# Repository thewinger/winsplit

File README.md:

# Winsplit

Inspired by the Boardrun Bizarre and Red herring. I wanted to be able to use a normal keyset, so no full ortho, but split.

## Disclaimer

This is my first designed keyboard from the grounds up.
I'm not responsible for any damage caused by using this keyboard or any production of this keyboard that doesn't work.

## Bill of materials

To be bought separately:

- 2x [RP2040 Pro Micro](https://es.aliexpress.com/item/1005006130019224.html).
- 70x pin headers
- 1x [Skyloong Rotary Encoder](https://es.aliexpress.com/item/1005005189266585.html?spm=a2g0o.order_list.order_list_main.122.376d194dW3x576&gatewayAdapt=glo2esp).
- 2x [TRRS Connector](https://es.aliexpress.com/item/33029465106.html).
- 2x [SMD Buttons](https://es.aliexpress.com/item/33013562004.html).
- 2x 128x32 [OLED panels](https://es.aliexpress.com/item/1005005973981064.html?spm=a2g0o.order_list.order_list_main.167.376d194dW3x576&gatewayAdapt=glo2esp).
- 73x [Kailh hotswap sockets](https://es.aliexpress.com/item/1005004290562374.html?spm=a2g0o.order_list.order_list_main.178.376d194dW3x576&gatewayAdapt=glo2esp).
- 73x [SK6812MINI-E leds](https://es.aliexpress.com/item/1005004908622116.html?spm=a2g0o.order_list.order_list_main.147.376d194dW3x576&gatewayAdapt=glo2esp).
- 4x 2u Stabilizers.
- 16x M2 6mm screws.

Diodes, capacitors, resistors and other small parts are to be soldered directly by JLCPCB. References in KiCad files.

## TODO

- [ ] **Rotate 180º right-side OLED connector.** Right now is not usable.
- [ ] **Rotary encoder.** As of now, it either works as a button when a normal switch is installed or as an encoder without button when the HS Skyloong encoder is installed.
- [ ] **Make screw holes in PCB 4mm instead of 2.2mm.** So they are passthrougth and bottom plate can be directly screwed to top plate, like lily58 or Corne keyboards.

## Notes

- Function keys (Right of B and left of N) are hard to reach.

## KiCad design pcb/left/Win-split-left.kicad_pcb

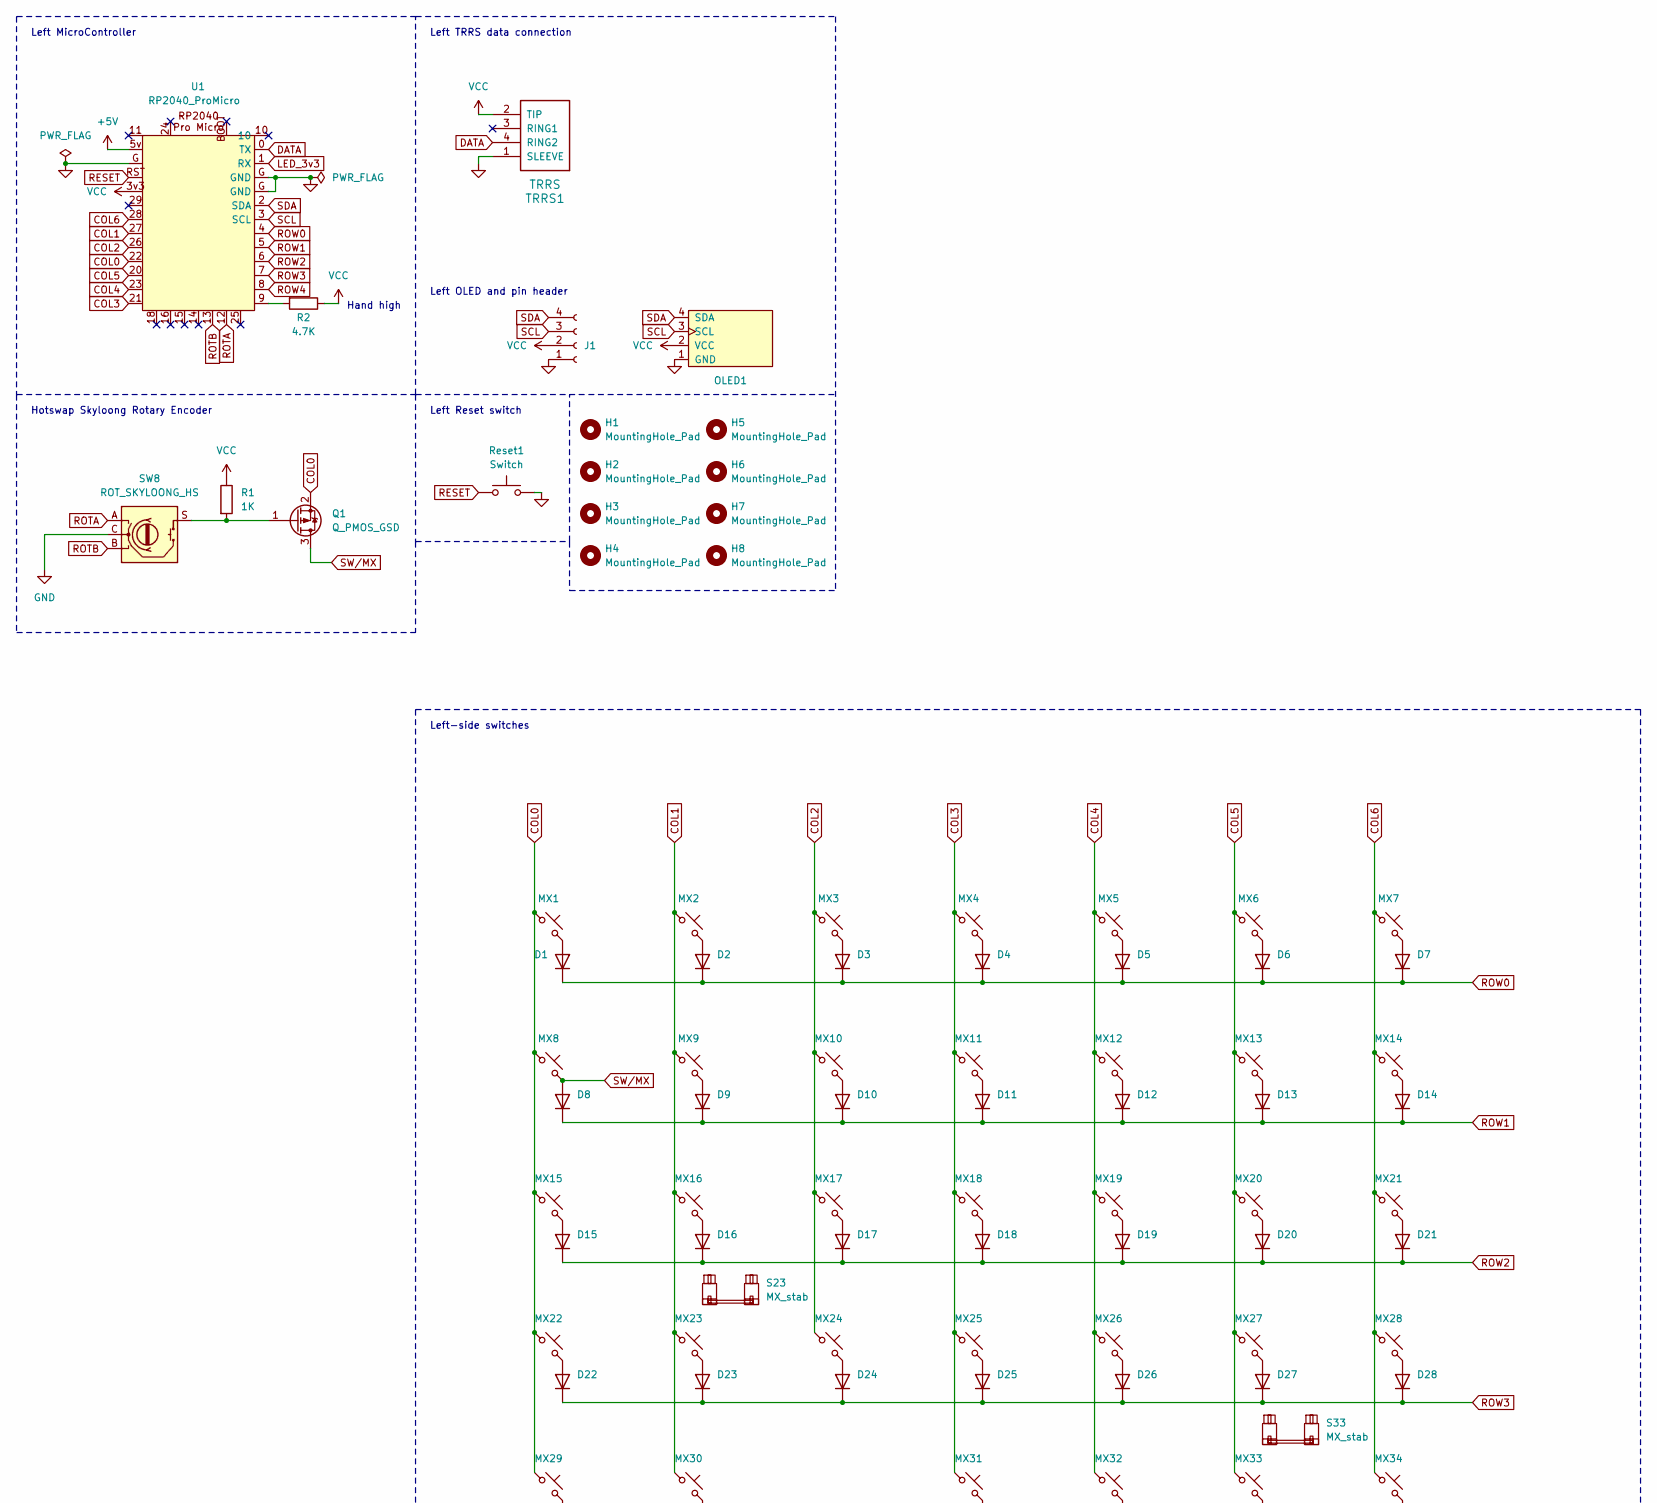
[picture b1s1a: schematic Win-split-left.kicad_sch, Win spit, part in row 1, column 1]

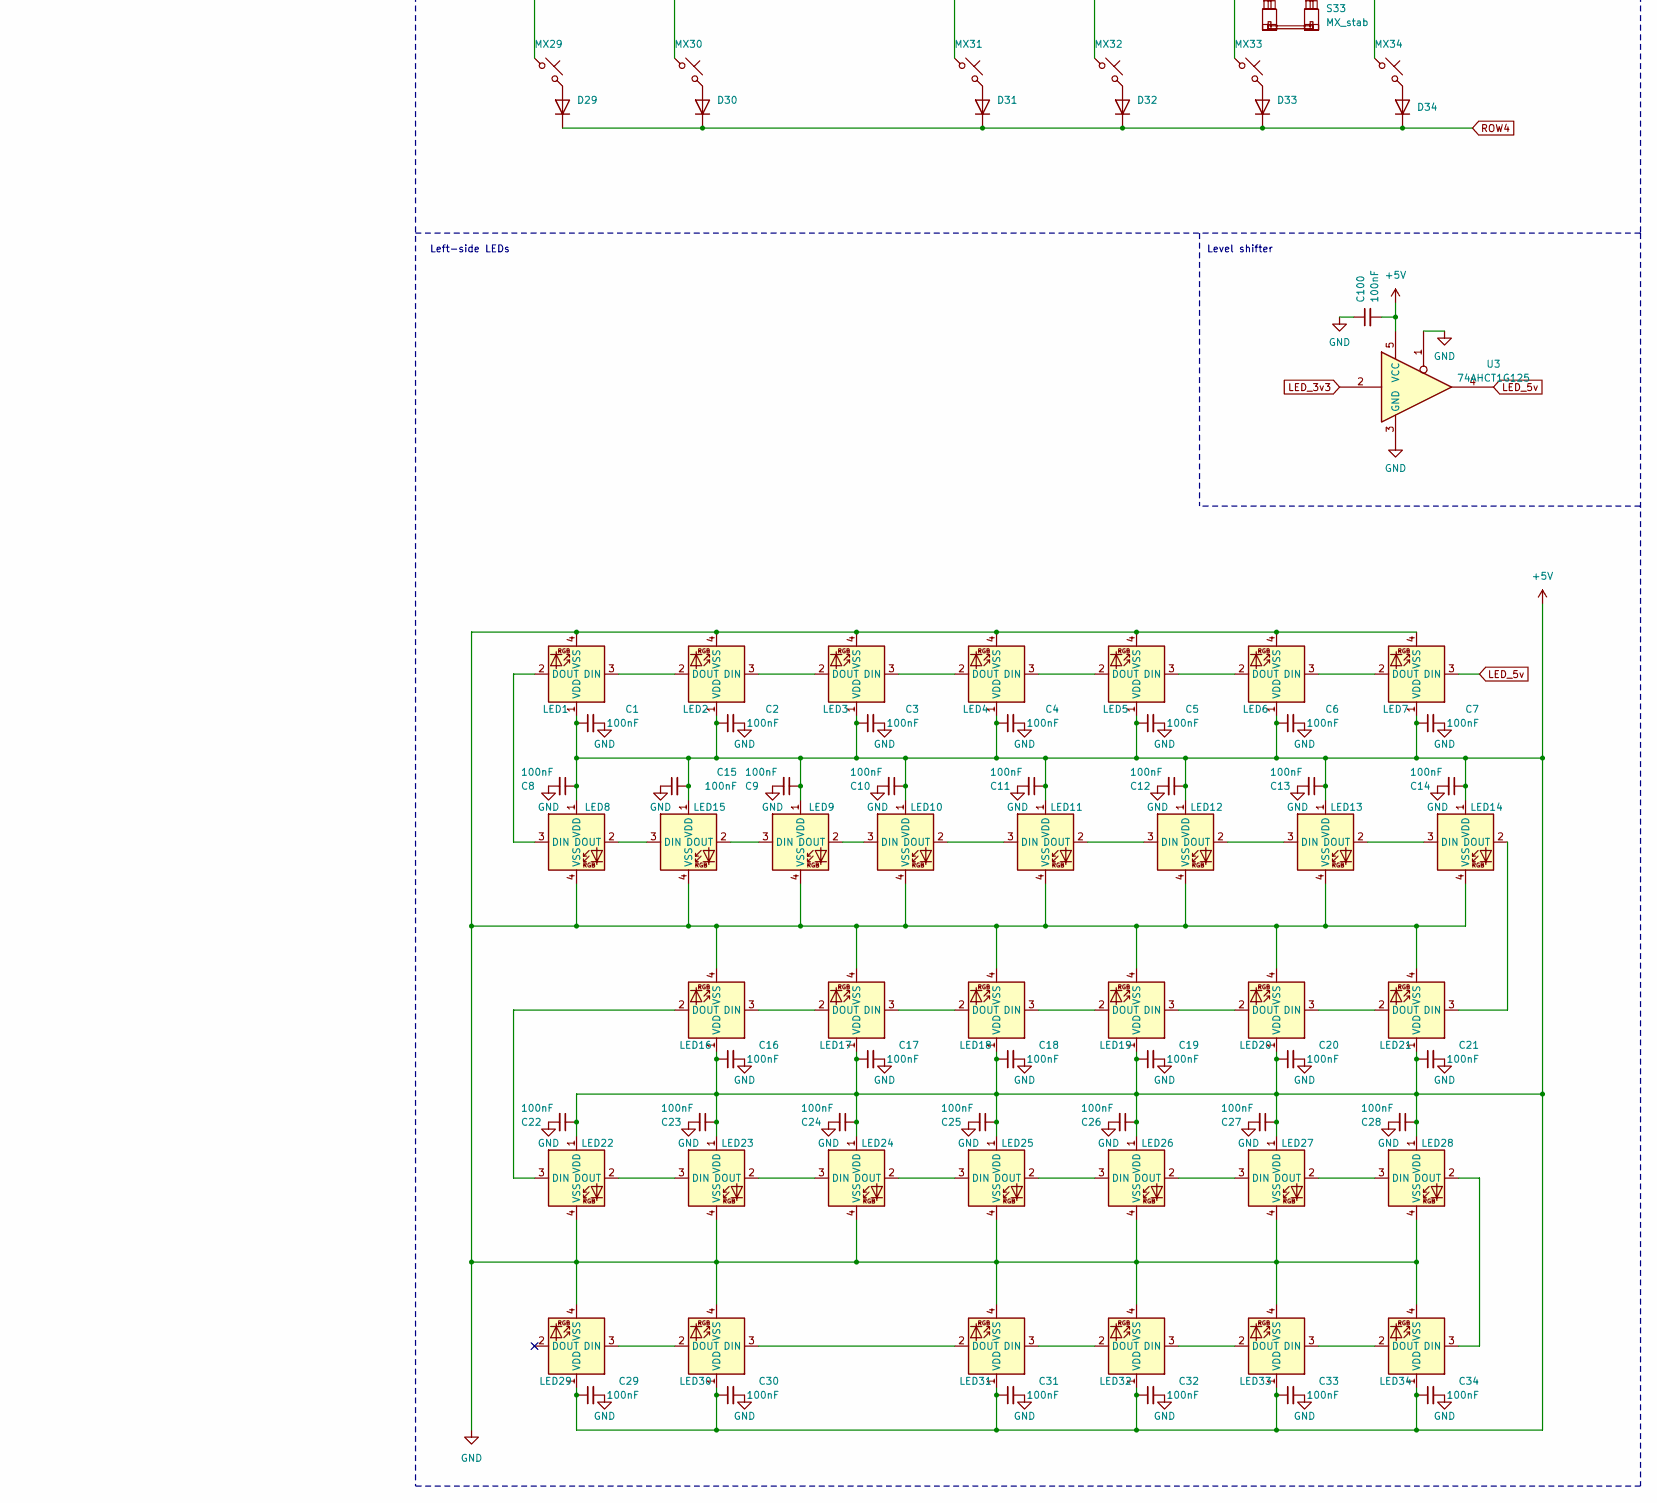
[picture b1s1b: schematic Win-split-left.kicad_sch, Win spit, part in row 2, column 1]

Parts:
C1, C2, C3, C4, C5, C6, C7, C8, C9, C10, C11, C12, C13, C14, C15, C16, C17, C18, C19, C20, C21, C22, C23, C24, C25, C26, C27, C28, C29, C30, C31, C32, C33, C34, C100: 100nF; C_0402_1005Metric; LCSC C1525
D1, D2, D3, D4, D5, D6, D7, D8, D9, D10, D11, D12, D13, D14, D15, D16, D17, D18, D19, D20, D21, D22, D23, D24, D25, D26, D27, D28, D29, D30, D31, D32, D33, D34: Diode; Diode_SOD-123; LCSC C81598
H1, H2, H3, H4, H5, H6, H7, H8: MountingHole_Pad; HOLE_M2
J1: Conn_01x04_Socket; PinHeader_1x04_P2.54mm_Vertical
LED1, LED2, LED3, LED4, LED5, LED6, LED7, LED8, LED16, LED17, LED18, LED19, LED20, LED21, LED22, LED29, LED30, LED31, LED32, LED33: MX_SK6812MINI-E; LED_MX_6028R
LED9, LED10, LED11, LED12, LED13, LED14, LED15, LED23, LED24, LED25, LED26, LED27, LED28, LED34: MX_SK6812MINI-E; LED_MX_6028R-ROT
MX1, MX2, MX3, MX4, MX5, MX6, MX7, MX8, MX10, MX11, MX12, MX13, MX14, MX15, MX17, MX18, MX19, MX20, MX21, MX22, MX23, MX24, MX25, MX26, MX27, MX28, MX29, MX33, MX34: MX_SW_HS; SW_MX_HS_CPG151101S11_1u
MX9: MX_SW_HS; SW_MX_HS_CPG151101S11_1.5u
MX16: MX_SW_HS; SW_MX_HS_CPG151101S11_1.75u
MX30, MX31, MX32: MX_SW_HS; SW_MX_HS_CPG151101S11_1.25u
OLED1: OLED_128x32
Q1: Q_PMOS_GSD; SOT-23; LCSC C133325
R1: 1K; R_0805_2012Metric; LCSC C17513
R2: 4.7K; R_0805_2012Metric; LCSC C17673
Reset1: Switch; SW_SPST_B3U-1000P; LCSC C231329
S23, S33: MX_stab; STAB_MX_P_2u
SW8: ROT_SKYLOONG_HS; ROT_SKYLOONG_HS-Switch
TRRS1: TRRS; TRRS_PJ-320A
U1: RP2040_ProMicro; RP2040_ProMicro_USBup
U3: 74AHCT1G125; SOT-23-5; LCSC C7484

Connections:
+5V: C1.1, C2.1, C3.1, C4.1, C5.1, C6.1, C7.1, C8.1, C9.1, C10.1, C11.1, C12.1, C13.1, C14.1, C15.2, C16.1, C17.1, C18.1, C19.1, C20.1, C21.1, C22.1, C23.1, C24.1, C25.1, C26.1, C27.1, C28.1, C29.1, C30.1, C31.1, C32.1, C33.1, C34.1, C100.2, LED1.1 (VDD), LED2.1 (VDD), LED3.1 (VDD), LED4.1 (VDD), LED5.1 (VDD), LED6.1 (VDD), LED7.1 (VDD), LED8.1 (VDD), LED9.1 (VDD), LED10.1 (VDD), LED11.1 (VDD), LED12.1 (VDD), LED13.1 (VDD), LED14.1 (VDD), LED15.1 (VDD), LED16.1 (VDD), LED17.1 (VDD), LED18.1 (VDD), LED19.1 (VDD), LED20.1 (VDD), LED21.1 (VDD), LED22.1 (VDD), LED23.1 (VDD), LED24.1 (VDD), LED25.1 (VDD), LED26.1 (VDD), LED27.1 (VDD), LED28.1 (VDD), LED29.1 (VDD), LED30.1 (VDD), LED31.1 (VDD), LED32.1 (VDD), LED33.1 (VDD), LED34.1 (VDD), U1.5v, U3.5 (VCC)
COL0: MX1.1, MX8.1, MX15.1, MX22.1, MX29.1, Q1.2 (S), U1.22
COL1: MX2.1, MX9.1, MX16.1, MX23.1, MX30.1, U1.27
COL2: MX3.1, MX10.1, MX17.1, MX24.1, U1.26
COL3: MX4.1, MX11.1, MX18.1, MX25.1, MX31.1, U1.21
COL4: MX5.1, MX12.1, MX19.1, MX26.1, MX32.1, U1.23
COL5: MX6.1, MX13.1, MX20.1, MX27.1, MX33.1, U1.20
COL6: MX7.1, MX14.1, MX21.1, MX28.1, MX34.1, U1.28
DATA: TRRS1.4 (RING2), U1.0 (TX)
GND: C1.2, C2.2, C3.2, C4.2, C5.2, C6.2, C7.2, C8.2, C9.2, C10.2, C11.2, C12.2, C13.2, C14.2, C15.1, C16.2, C17.2, C18.2, C19.2, C20.2, C21.2, C22.2, C23.2, C24.2, C25.2, C26.2, C27.2, C28.2, C29.2, C30.2, C31.2, C32.2, C33.2, C34.2, C100.1, J1.1, LED1.4 (VSS), LED2.4 (VSS), LED3.4 (VSS), LED4.4 (VSS), LED5.4 (VSS), LED6.4 (VSS), LED7.4 (VSS), LED8.4 (VSS), LED9.4 (VSS), LED10.4 (VSS), LED11.4 (VSS), LED12.4 (VSS), LED13.4 (VSS), LED14.4 (VSS), LED15.4 (VSS), LED16.4 (VSS), LED17.4 (VSS), LED18.4 (VSS), LED19.4 (VSS), LED20.4 (VSS), LED21.4 (VSS), LED22.4 (VSS), LED23.4 (VSS), LED24.4 (VSS), LED25.4 (VSS), LED26.4 (VSS), LED27.4 (VSS), LED28.4 (VSS), LED29.4 (VSS), LED30.4 (VSS), LED31.4 (VSS), LED32.4 (VSS), LED33.4 (VSS), LED34.4 (VSS), OLED1.1 (GND), Reset1.2, SW8.C, TRRS1.1 (SLEEVE), U1.G (GND), U3.1, U3.3 (GND)
LED_3v3: U1.1 (RX), U3.2
LED_5v: LED7.3 (DIN), U3.4
unnamed: D1.2 (A), MX1.2
unnamed: D2.2 (A), MX2.2
unnamed: D3.2 (A), MX3.2
unnamed: D4.2 (A), MX4.2
unnamed: D5.2 (A), MX5.2
unnamed: D6.2 (A), MX6.2
unnamed: D7.2 (A), MX7.2
unnamed: D9.2 (A), MX9.2
unnamed: D10.2 (A), MX10.2
unnamed: D11.2 (A), MX11.2
unnamed: D12.2 (A), MX12.2
unnamed: D13.2 (A), MX13.2
unnamed: D14.2 (A), MX14.2
unnamed: D15.2 (A), MX15.2
unnamed: D16.2 (A), MX16.2
unnamed: D17.2 (A), MX17.2
unnamed: D18.2 (A), MX18.2
unnamed: D19.2 (A), MX19.2
unnamed: D20.2 (A), MX20.2
unnamed: D21.2 (A), MX21.2
unnamed: D22.2 (A), MX22.2
unnamed: D23.2 (A), MX23.2
unnamed: D24.2 (A), MX24.2
unnamed: D25.2 (A), MX25.2
unnamed: D26.2 (A), MX26.2
unnamed: D27.2 (A), MX27.2
unnamed: D28.2 (A), MX28.2
unnamed: D29.2 (A), MX29.2
unnamed: D30.2 (A), MX30.2
unnamed: D31.2 (A), MX31.2
unnamed: D32.2 (A), MX32.2
unnamed: D33.2 (A), MX33.2
unnamed: D34.2 (A), MX34.2
unnamed: LED1.3 (DIN), LED2.2 (DOUT)
unnamed: LED1.2 (DOUT), LED8.3 (DIN)
unnamed: LED2.3 (DIN), LED3.2 (DOUT)
unnamed: LED3.3 (DIN), LED4.2 (DOUT)
unnamed: LED4.3 (DIN), LED5.2 (DOUT)
unnamed: LED5.3 (DIN), LED6.2 (DOUT)
unnamed: LED6.3 (DIN), LED7.2 (DOUT)
unnamed: LED9.2 (DOUT), LED10.3 (DIN)
unnamed: LED10.2 (DOUT), LED11.3 (DIN)
unnamed: LED11.2 (DOUT), LED12.3 (DIN)
unnamed: LED12.2 (DOUT), LED13.3 (DIN)
unnamed: LED13.2 (DOUT), LED14.3 (DIN)
unnamed: LED14.2 (DOUT), LED21.3 (DIN)
unnamed: LED8.2 (DOUT), LED15.3 (DIN)
unnamed: LED9.3 (DIN), LED15.2 (DOUT)
unnamed: LED16.3 (DIN), LED17.2 (DOUT)
unnamed: LED16.2 (DOUT), LED22.3 (DIN)
unnamed: LED17.3 (DIN), LED18.2 (DOUT)
unnamed: LED18.3 (DIN), LED19.2 (DOUT)
unnamed: LED19.3 (DIN), LED20.2 (DOUT)
unnamed: LED20.3 (DIN), LED21.2 (DOUT)
unnamed: LED22.2 (DOUT), LED23.3 (DIN)
unnamed: LED23.2 (DOUT), LED24.3 (DIN)
unnamed: LED24.2 (DOUT), LED25.3 (DIN)
unnamed: LED25.2 (DOUT), LED26.3 (DIN)
unnamed: LED26.2 (DOUT), LED27.3 (DIN)
unnamed: LED27.2 (DOUT), LED28.3 (DIN)
unnamed: LED28.2 (DOUT), LED34.3 (DIN)
unnamed: LED29.3 (DIN), LED30.2 (DOUT)
unnamed: LED30.3 (DIN), LED31.2 (DOUT)
unnamed: LED31.3 (DIN), LED32.2 (DOUT)
unnamed: LED32.3 (DIN), LED33.2 (DOUT)
unnamed: LED33.3 (DIN), LED34.2 (DOUT)
unnamed: Q1.1 (G), R1.2, SW8.S
unnamed: R2.2, U1.9
RESET: Reset1.1, U1.RST
ROTA: SW8.A, U1.12
ROTB: SW8.B, U1.13
ROW0: D1.1 (K), D2.1 (K), D3.1 (K), D4.1 (K), D5.1 (K), D6.1 (K), D7.1 (K), U1.4
ROW1: D8.1 (K), D9.1 (K), D10.1 (K), D11.1 (K), D12.1 (K), D13.1 (K), D14.1 (K), U1.5
ROW2: D15.1 (K), D16.1 (K), D17.1 (K), D18.1 (K), D19.1 (K), D20.1 (K), D21.1 (K), U1.6
ROW3: D22.1 (K), D23.1 (K), D24.1 (K), D25.1 (K), D26.1 (K), D27.1 (K), D28.1 (K), U1.7
ROW4: D29.1 (K), D30.1 (K), D31.1 (K), D32.1 (K), D33.1 (K), D34.1 (K), U1.8
SCL: J1.3, OLED1.3 (SCL), U1.3 (SCL)
SDA: J1.4, OLED1.4 (SDA), U1.2 (SDA)
SW/MX: D8.2 (A), MX8.2, Q1.3 (D)
VCC: J1.2, OLED1.2 (VCC), R1.1, R2.1, TRRS1.2 (TIP), U1.3v3

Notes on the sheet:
Left-side switches
Left MicroController
Left Reset switch
Left OLED and pin header
Level shifter
Left-side LEDs
Hand high
Left TRRS data connection
Hotswap Skyloong Rotary Encoder

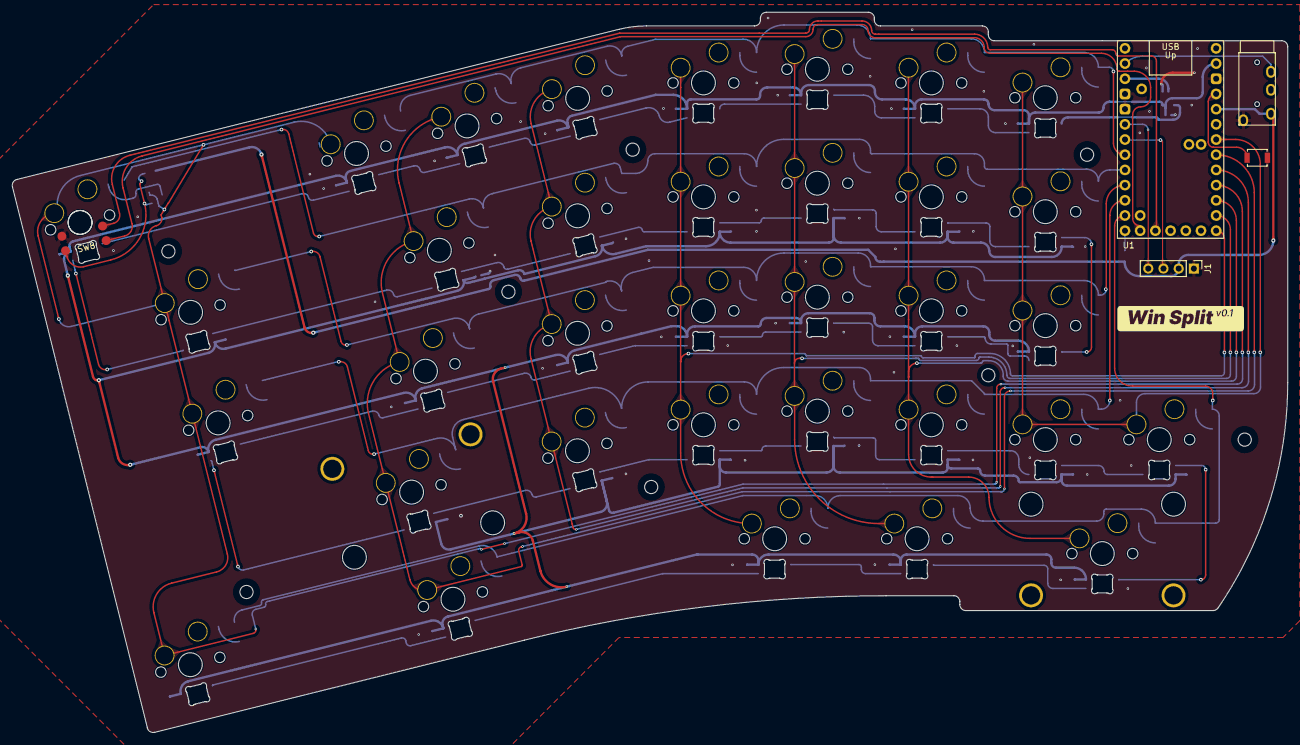
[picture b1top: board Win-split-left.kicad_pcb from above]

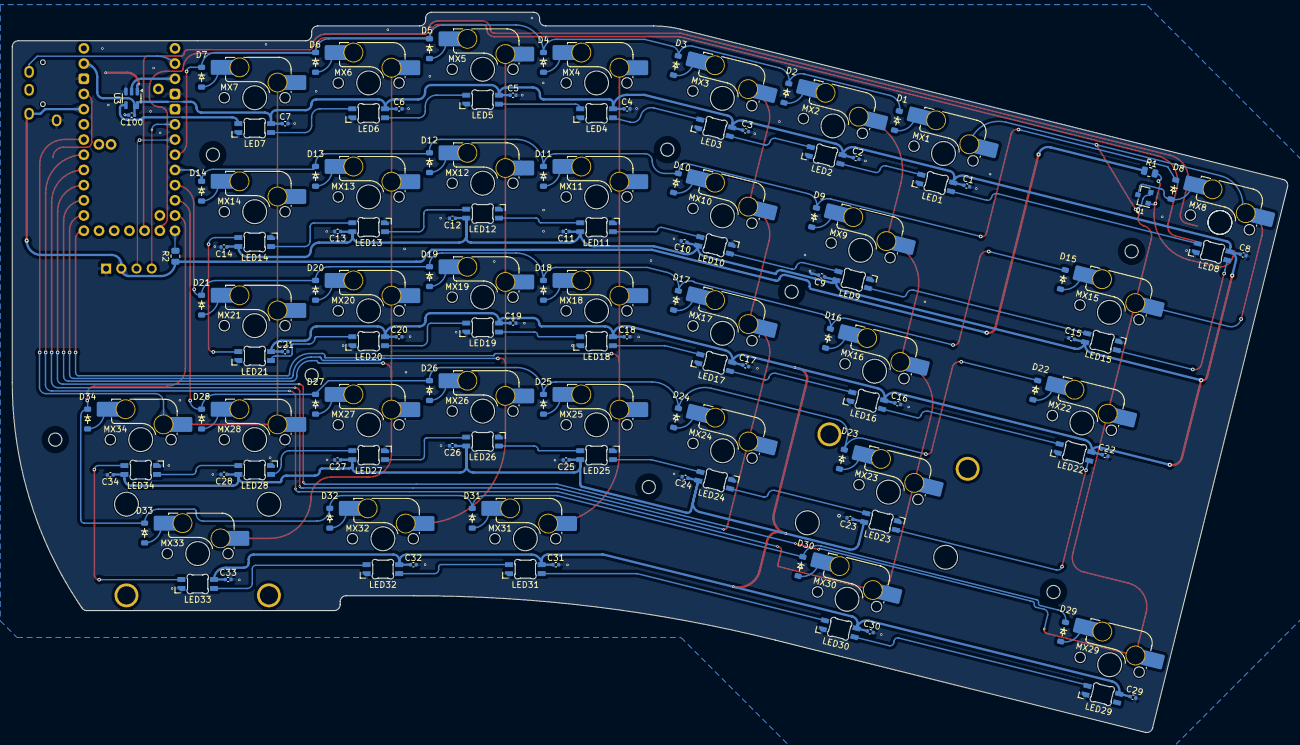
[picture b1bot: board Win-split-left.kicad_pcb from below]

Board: 2 copper layers, 213.2 x 120.4 mm, 156 parts (141 on the bottom side), 92 nets.

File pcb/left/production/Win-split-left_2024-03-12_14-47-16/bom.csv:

Designator,Footprint,Quantity,Value,LCSC Part #
"C1, C10, C100, C11, C12, C13, C14, C15, C16, C17, C18, C19, C2, C20, C21, C22, C23, C24, C25, C26, C27, C28, C29, C3, C30, C31, C32, C33, C34, C4, C5, C6, C7, C8, C9",0402,35,100nF,C1525
"D1, D10, D11, D12, D13, D14, D15, D16, D17, D18, D19, D2, D20, D21, D22, D23, D24, D25, D26, D27, D28, D29, D3, D30, D31, D32, D33, D34, D4, D5, D6, D7, D8, D9",Diode_SOD-123,34,Diode,C81598
ESD1,SOT-23-6-routable,1,SRV05-4,C558418
"H1, H2, H3, H4, H5, H6, H7, H8",HOLE_M2,8,MountingHole_Pad,
J1,PinHeader_1x04_P2.54mm_Vertical,1,Conn_01x04_Socket,
"LED1, LED16, LED17, LED18, LED19, LED2, LED20, LED21, LED22, LED29, LED3, LED30, LED31, LED32, LED33, LED4, LED5, LED6, LED7, LED8",LED_MX_6028R,20,MX_SK6812MINI-E,
"LED10, LED11, LED12, LED13, LED14, LED15, LED23, LED24, LED25, LED26, LED27, LED28, LED34, LED9",LED_MX_6028R-ROT,14,MX_SK6812MINI-E,
"MX1, MX10, MX11, MX12, MX13, MX14, MX15, MX17, MX18, MX19, MX2, MX20, MX21, MX22, MX23, MX24, MX25, MX26, MX27, MX28, MX29, MX3, MX33, MX34, MX4, MX5, MX6, MX7, MX8",SW_MX_HS_CPG151101S11_1u,29,MX_SW_HS,
MX16,SW_MX_HS_CPG151101S11_1.75u,1,MX_SW_HS,
"MX30, MX31, MX32",SW_MX_HS_CPG151101S11_1.25u,3,MX_SW_HS,
MX9,SW_MX_HS_CPG151101S11_1.5u,1,MX_SW_HS,
Q1,SOT-23,1,Q_PMOS_GSD,C133325
R1,0805,1,1K,C17513
R2,0805,1,4.7K,C17673
Reset1,SW_SPST_B3U-1000P,1,Switch,C231329
"S23, S33",STAB_MX_P_2u,2,MX_stab,
TRRS1,TRRS_PJ-320A,1,TRRS,
U1,RP2040_ProMicro_USBup,1,RP2040_ProMicro,
U3,SOT-23-5,1,74AHCT1G125,C7484

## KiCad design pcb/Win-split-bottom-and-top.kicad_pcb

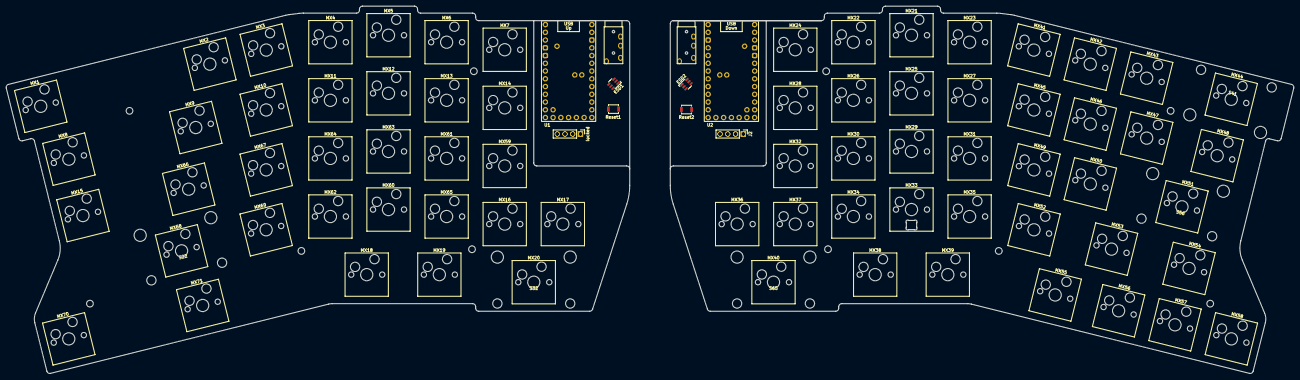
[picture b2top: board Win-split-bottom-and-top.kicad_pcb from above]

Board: 2 copper layers, 422.1 x 120.4 mm, 99 parts (1 on the bottom side), 28 nets, no tracks yet.

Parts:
ESD1, ESD2: SRV05-4; SOT-23-6-routable
H1, H2, H3, H4, H5, H6, H7, H8, H9, H10: MountingHole_Pad; HOLE_M2
J2: Conn_01x04_Socket; PinHeader_1x04_P2.54mm_Vertical
LED59: MX_SK6812MINI-E; LED_MX_6028R
MX1, MX2, MX3, MX4, MX5, MX6, MX7, MX8, MX10, MX11, MX12, MX13, MX14, MX15, MX17, MX18, MX19, MX20, MX21, MX23, MX24, MX25, MX26, MX27, MX28, MX33, MX34, MX35, MX36, MX37, MX38, MX39, MX40, MX42, MX43, MX44, MX45, MX46, MX47, MX48, MX50, MX51, MX52, MX53, MX54, MX55, MX57, MX58, MX59, MX60, MX61, MX63, MX64, MX69, MX70, MX71: MX_SW_HS; Hotswap_MX_1.00u
MX9, MX49: MX_SW_HS; Hotswap_MX_1.50u
MX16, MX62: MX_SW_HS; Hotswap_MX_1.75u
MX22, MX32, MX41: MX_SW_HS; Hotswap_MX_2.00u
MX29, MX30, MX31, MX66, MX67, MX68: MX_SW_HS; Hotswap_MX_1.25u
MX56, MX65: MX_SW_HS; Hotswap_MX_2.25u
OLED1: locked; OLED_128x32
OLED2: OLED_128x32
Reset1, Reset2: Switch; SW_SPST_B3U-1000P
S22, S32, S41, S56, S65: MX_stab; Stabilizer_MX_2.00u
TRRS1, TRRS2: TRRS; TRRS_PJ-320A
U1: RP2040_ProMicro; RP2040_ProMicro_USBup
U2: RP2040_ProMicro; RP2040_ProMicro_USBdn
locked: Conn_01x04_Socket; PinHeader_1x04_P2.54mm_Vertical

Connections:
+5V: LED59.1 (VDD), U1.5v
ColL 0: MX1.1, MX8.1, MX15.1, MX28.1, U1.28
ColL 1: MX2.1, MX9.1, MX16.1, MX22.1, MX29.1, U1.27
ColL 2: MX3.1, MX10.1, MX17.1, MX23.1, U1.26
ColL 3: MX4.1, MX11.1, MX18.1, MX24.1, MX30.1, U1.22
ColL 4: MX5.1, MX12.1, MX19.1, MX25.1, MX31.1, U1.20
ColL 5: MX6.1, MX13.1, MX20.1, MX26.1, MX32.1, U1.23
ColL 6: MX7.1, MX14.1, MX21.1, MX27.1, MX33.1, U1.21
ColR 0: MX34.1, MX42.1, MX50.1, MX57.1, MX64.1, U2.29
ColR 1: MX35.1, MX43.1, MX51.1, MX58.1, MX65.1, U2.28
ColR 2: MX36.1, MX44.1, MX52.1, MX59.1, MX66.1, U2.27
ColR 3: MX37.1, MX45.1, MX53.1, MX60.1, MX67.1, U2.26
ColR 4: MX38.1, MX46.1, MX54.1, MX61.1, MX68.1, U2.22
ColR 5: MX39.1, MX47.1, MX55.1, MX62.1, MX69.1, U2.20
ColR 6: MX40.1, MX48.1, MX56.1, MX63.1, MX70.1, U2.23
ColR 7: MX41.1, MX49.1, MX71.1, U2.21
DATA1: ESD1.4 (IO3), U1.0 (TX)
DATA2: ESD2.4 (IO3), U2.0 (TX)
GND: ESD1.2 (VN), ESD2.2 (VN), J2.1, LED59.4 (VSS), OLED1.1 (GND), OLED2.1 (GND), Reset1.2, Reset2.2, TRRS1.4 (RING2), TRRS2.4 (RING2), U1.G (GND), U2.9, U2.G, locked.1
unnamed: ESD1.1 (IO1), TRRS1.3 (RING1)
unnamed: ESD2.1 (IO1), TRRS2.3 (RING1)
Reset1: Reset1.1, U1.RST
Reset2: Reset2.1, U2.RST
SCL1: OLED1.3 (SCL), U1.3 (SCL), locked.3
SCL2: J2.3, OLED2.3 (SCL), U2.3 (SCL)
SDA1: OLED1.4 (SDA), U1.2 (SDA), locked.4
SDA2: J2.4, OLED2.4 (SDA), U2.2 (SDA)
VCC: ESD1.5 (VP), ESD2.5 (VP), J2.2, OLED1.2 (VCC), OLED2.2 (VCC), TRRS1.1 (SLEEVE), TRRS2.1 (SLEEVE), U1.3v3, U1.9, U2.3v3, locked.2

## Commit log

2024-02-08 up to rotary
2024-02-08 adds resources
2024-02-25 pre-del button
2024-03-01 separated in 2 pcbs
2024-03-08 kicad 7
2024-03-12 before rounding tracks in left side
2024-03-13 prerouting right side
2024-04-10 designed
2024-05-27 vial firmware and 3D cases
2024-05-27 adds readme
2024-05-27 format readme
2024-05-27 adds bill of materials to readme
